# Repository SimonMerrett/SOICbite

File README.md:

# SOICbite
A compact PCB footprint which allows SOIC test clips to be used as a space-efficient programming and debugging connector

This is the repository for a hackaday.io project on this connector footprint.

It's cheaper than a Tag Connect and may even be smaller. 

This has been tested as a SPI programmer on AVRs and a UART programmer on ESP32.

The footprints are available in the following formats:

- Kicad (.kicad_mod)
- Eagle XML (.lbr)
- gEDA PCB (.fp)
- pcb-rnd (.lht)

and more formats are welcome.

You do need to [adjust your SOIC-8 test clip](https://github.com/SimonMerrett/SOICbite/blob/master/HOWTO_mod_clip.md) so that it will close enough to press the contact pins against the PCB pads. See the photos in the images folder - about 1mm will do to start with. Depending on your pin configuration, you need to make sure opposing contacts don't touch each other when no PCB is between them. 

Also, you may need to use short sections of thin traces to escape the pads between the NPTH.

# Pin assignment

If you don't know where to start, here are a few suggestions for pin assignments of some interfaces:

| Pin | UART | SPI       | SWIM | SWD   | ESP8266     | USB | I2C | PIC ICSP | JTAG | SWD + UART | UPDI |
| --- | ---- | --------- | ---- | ----- | ----------- | --- | --- | -------- | ---- | ---------- | ---- |
| 1   | Vcc  | Vcc       | Vcc  | Vcc   | Vcc         | Vcc | Vcc | Vcc      | Vcc  | Vcc        | Vcc  |
| 2   | RX2  | CS        |      |       | GPIO0       | D-  |     | Vpp      | TMS  | RX         |      |
| 3   | TX2  |           |      |       | GPIO2       | D+  |     |          | TCK  | TX         |      |
| 4   | GND  | GND       | GND  | GND   | GND         | GND | GND | GND      | GND  | GND        | GND  |
| 5   | RX   | MOSI/MOMI | SWIM | SWDIO | RX          |     | SDA | DAT      | TDI  | SWDIO      | UPDI |
| 6   | TX   | MISO      |      | SWO   | TX          |     |     | AUX      | TDO  | SWO        |      |
| 7   | CTS  | SCK/CLK   |      | SWCLK | CH_PD       |     | SCL | CLK      | RTCK | SWCLK      |      |
| 8   | RTS  | RST       | NRST | NRST  | RST         | ID  |     |          | NRST | NRST       |      |

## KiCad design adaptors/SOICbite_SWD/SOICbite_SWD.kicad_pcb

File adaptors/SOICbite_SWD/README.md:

# SOICbite SWD Breakout

SOICbite to SWD breakout board:

1. Standard Cortex Debug connector - VCC, GND, SWDIO, SWCLK, SWO and NRST pins are broken out
2. 4-Pin 2.54" Header - VCC, SWDIO, SWCLK, GND are broken out

## 3D Renders

## Images

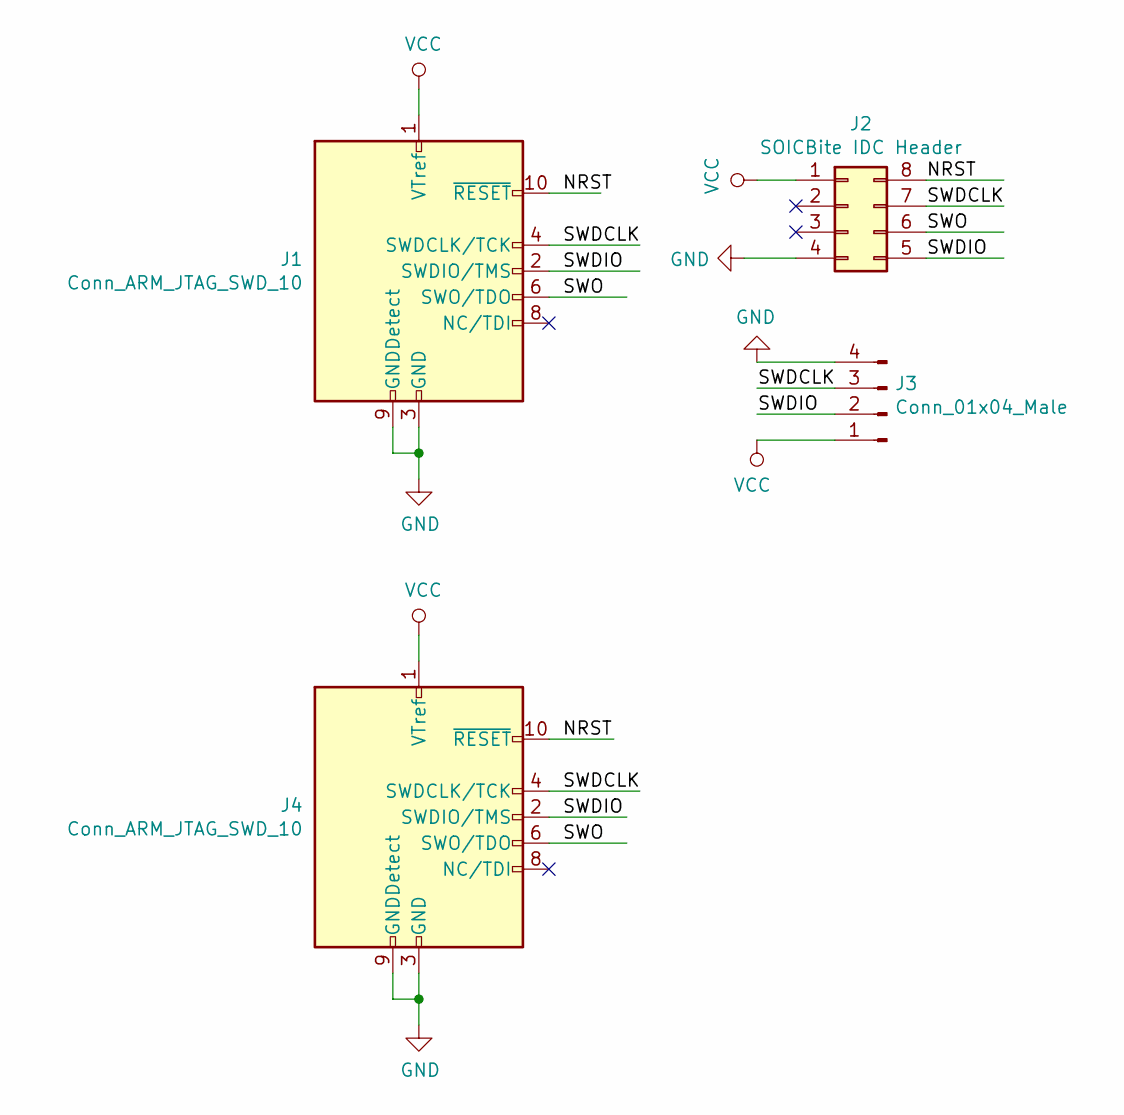
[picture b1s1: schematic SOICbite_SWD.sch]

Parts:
J1: Conn_ARM_JTAG_SWD_10; PinHeader_2x05_P1.27mm_Vertical_SMD
J2: SOICBite IDC Header; IDC-Header_2x04_P2.54mm_Vertical
J3: Conn_01x04_Male; PinHeader_1x04_P2.54mm_Vertical
J4: Conn_ARM_JTAG_SWD_10; PinHeader_2x05_P1.27mm_Vertical

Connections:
/NRST: J1.10 (~RESET~), J2.8, J4.10 (~RESET~)
/SWDCLK: J1.4 (SWDCLK/TCK), J2.7, J3.3, J4.4 (SWDCLK/TCK)
/SWDIO: J1.2 (SWDIO/TMS), J2.5, J3.2, J4.2 (SWDIO/TMS)
/SWO: J1.6 (SWO/TDO), J2.6, J4.6 (SWO/TDO)
GND: J1.3 (GND), J1.5 (GND), J1.9 (GNDDetect), J2.4, J3.4, J4.3 (GND), J4.5 (GND), J4.9 (GNDDetect)
VCC: J1.1 (VTref), J2.1, J3.1, J4.1 (VTref)

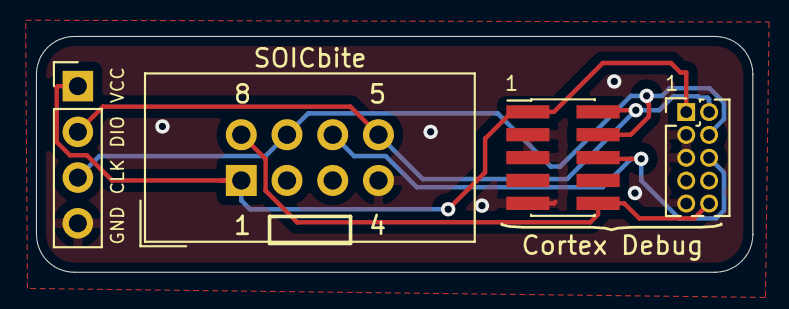
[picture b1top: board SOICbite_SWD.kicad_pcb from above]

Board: 2 copper layers, 39.8 x 13.1 mm, 4 parts (0 on the bottom side), 6 nets.

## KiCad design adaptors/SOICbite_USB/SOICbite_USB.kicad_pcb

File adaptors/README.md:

# Adaptors

Opinionated boards to breakout the SOICbite connections to standard interface pin arrangements.

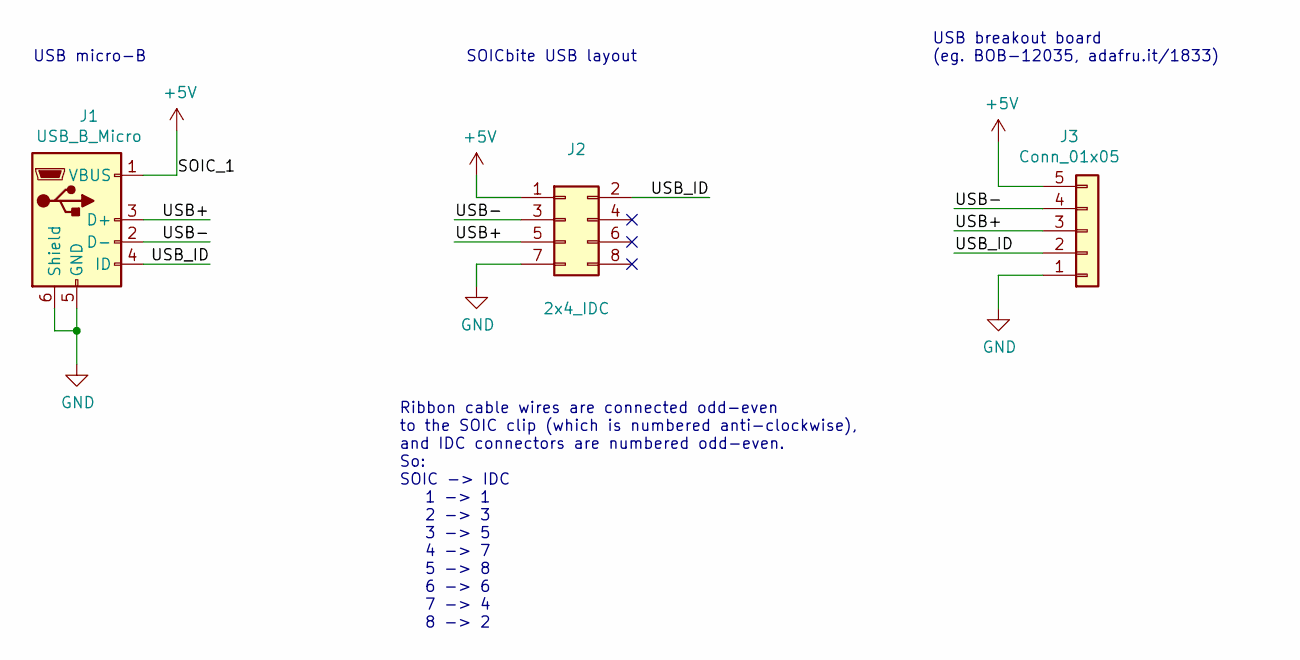
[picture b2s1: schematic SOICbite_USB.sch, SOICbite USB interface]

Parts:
J1: USB_B_Micro; USB_Micro-B_Wuerth_614105150721_Vertical; MPN 614 105 150 721; farnell 2470821
J2: 2x4_IDC; IDC-Header_2x04_P2.54mm_Vertical; MPN 61200821621; farnell 2356252
J3: Conn_01x05; PinHeader_1x05_P2.54mm_Vertical

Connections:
+5V: J1.1 (VBUS), J2.1, J3.5
/USB+: J1.3 (D+), J2.5, J3.3
/USB-: J1.2 (D-), J2.3, J3.4
/USB_ID: J1.4 (ID), J2.2, J3.2
GND: J1.5 (GND), J1.6 (Shield), J2.7, J3.1

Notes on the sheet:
USB micro-B
SOICbite USB layout
USB breakout board (eg. BOB-12035, adafru.it/1833)
Ribbon cable wires are connected odd-even to the SOIC clip (which is numbered anti-clockwise), and IDC connectors are numbered odd-even. So: SOIC -> IDC 1 -> 1 2 -> 3 3 -> 5 4 -> 7 5 -> 8 6 -> 6 7 -> 4 8 -> 2

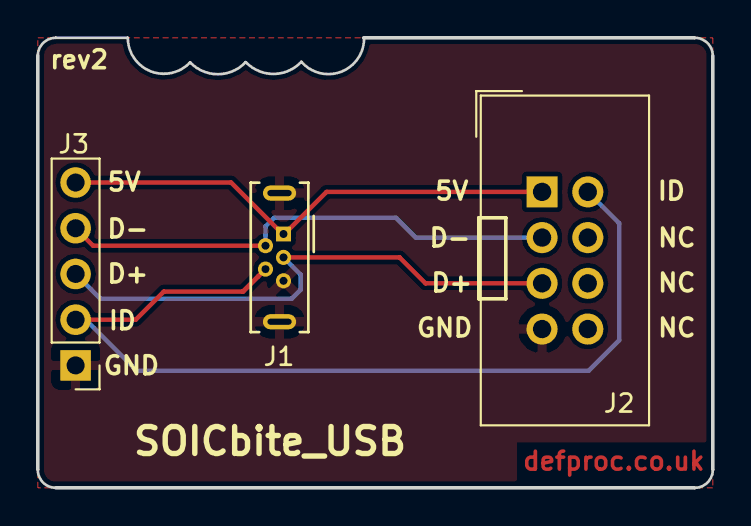
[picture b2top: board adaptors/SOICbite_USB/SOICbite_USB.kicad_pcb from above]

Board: 2 copper layers, 37.5 x 25.0 mm, 3 parts (0 on the bottom side), 5 nets.

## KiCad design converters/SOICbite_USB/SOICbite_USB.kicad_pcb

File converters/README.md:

#Converters

Opinionated boards to breakout the SOICbite connections to standard interface pin arrangements.

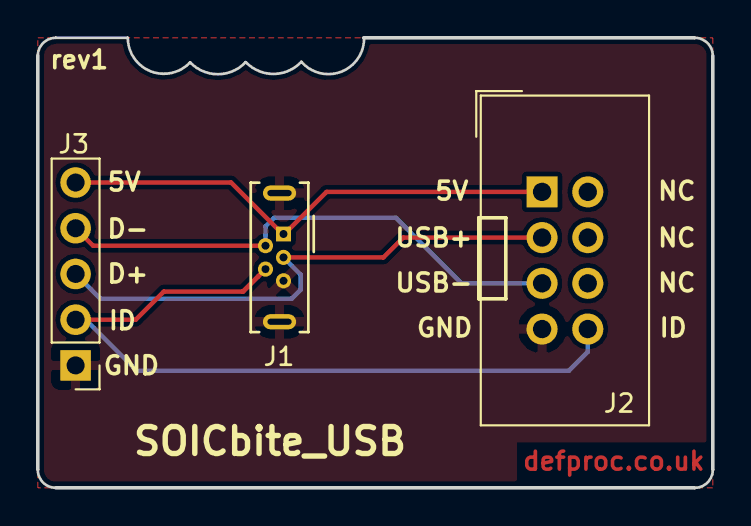
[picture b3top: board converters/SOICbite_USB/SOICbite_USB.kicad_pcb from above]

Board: 2 copper layers, 37.5 x 25.0 mm, 3 parts (0 on the bottom side), 5 nets.

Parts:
J1: USB_B_Micro; USB_Micro-B_Wuerth_614105150721_Vertical
J2: 2x4_IDC; IDC-Header_2x04_P2.54mm_Vertical
J3: Conn_01x05; PinHeader_1x05_P2.54mm_Vertical

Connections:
+5V: J1.1, J2.1, J3.5
/USB+: J1.3, J2.3, J3.3
/USB-: J1.2, J2.5, J3.4
/USB_ID: J1.4, J2.8, J3.2
GND: J1.5, J1.6, J2.7, J3.1

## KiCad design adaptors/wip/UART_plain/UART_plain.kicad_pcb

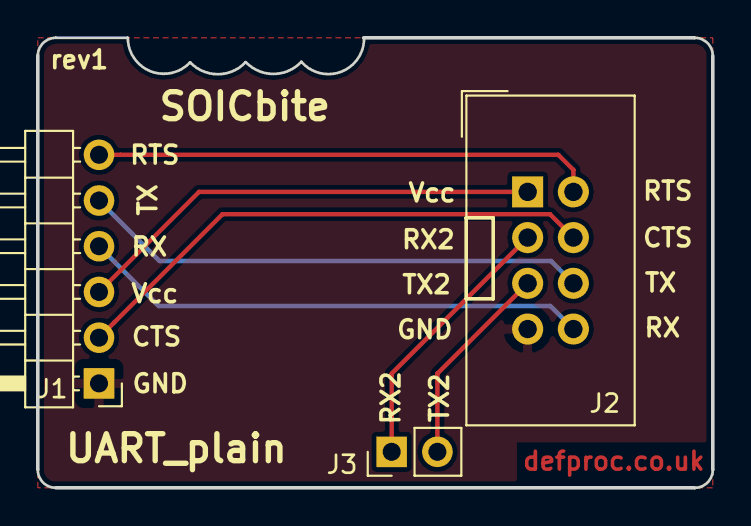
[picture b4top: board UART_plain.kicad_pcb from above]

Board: 2 copper layers, 37.5 x 25.0 mm, 3 parts (0 on the bottom side), 8 nets.

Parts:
J1: UART adaptor; PinHeader_1x06_P2.54mm_Horizontal
J2: 2x4_IDC; IDC-Header_2x04_P2.54mm_Vertical
J3: UART2; PinHeader_1x02_P2.54mm_Vertical

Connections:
/CTS: J1.2, J2.4
/RTS: J1.6, J2.2
/RX: J1.4, J2.8
/RX2: J2.3, J3.1
/TX: J1.5, J2.6
/TX2: J2.5, J3.2
GND: J1.1, J2.7
VDD: J1.3, J2.1

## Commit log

2019-06-03 Upload SOICbite kicad_mod footprint file
2019-06-03 create folder
2019-06-03 upload image files
2019-06-03 Removed ref to Github, as text was copied from HaD.io
2019-06-13 Purpose a pin assignment
    This is just a starting point to suggest a pin assignment for this
    connector. It would be great if every project with a SOICbite connector
    could be used similar, with the same programmer. Anyhow, a "version 1"
    probably should be discussed somehow with all the pros and cons. This
    one uses the SPI pinout of an AVR AT-Tiny and tries to assign similar
    functions from other interfaces to the same pins.
2019-06-14 Swapping pin 1 - pin 8
2019-06-17 Recreated Footprint within Eagle along with a simple Symbol for EAGLE users in .lbr form. Review added images for footprint and library/component description
2019-06-17 Corrected filename
2019-06-17 Corrected Description inconsistency
2019-06-17 Typo correction. Footprint cleanup.
2019-07-23 SOICbite to USB converter board, rev1
2019-07-23 include render of USB interface board
2019-07-23 do markdown properly
2019-08-02 rev1 of a plain IDC to UART adaptor
2019-08-05 SOICbite_USB is works in testing, moved UART_plain to wip directory, kicad gitignore
2019-08-13 removed wip, moved to wip_uart branch
2019-08-13 rev2 layout, moved USB_ID to SOICbite pin 8
2019-08-13 revised pinout, D- should be by Vcc
2019-08-13 added USB pinout
2019-08-13 and update the silkscreen to match the D+/D- swap
2019-08-14 Fixed possible typo in Adapter/adaptor
2019-09-28 Added suggested pinout for I2C
2019-09-29 Add SOICbite to SWD adaptor board
2019-11-11 Update README.md
    added NRST to SWD suggested pinout
2019-11-11 Added images for SWD breakout
2019-12-13 Added recommend PIC ICSP pinout
2019-12-20 Clarified "PIC ICSP" instead of any other kind
2020-03-28 Create LICENSE
2020-04-16 Add clip edge detailed image
    May be useful for someone wanting to see better how to trim down their clip
2020-04-16 Create HOWTO_mod_clip.md
    May be helpful for people to visualise the trimming requirement.
2020-04-16 Add README link to HOWTO
2020-06-02 Upload drawing to indicate board edges
    Careful - these dimensions have yet to be fully confirmed but you should be fine using them to make your own footprint from.
2020-06-20 kicad: add courtyard around symbol
    It is good to have courtyard defined as DRC might use it to catch errors
    when components are missing. While it doesn't sound that useful for this
    particular part, the DRC might actually complain about it being missing
    if its turned on for the project.
    The courtyard layer is defined on:
    https://kicad-pcb.org/libraries/klc/F5.3/
2021-02-11 add gEDA footprint and symbol
2021-02-11 add gerbers and images for gEDA footprint
2021-02-11 remove backup files
2022-04-21 Add footprint for pcb-rnd
2022-04-21 Mention various formats available
2022-04-21 Update readme with avaliable formats
2022-04-21 Update README with available formats
2023-11-25 Add JTAG pin specification
2024-11-02 Add SWD+UART pin assignment
2025-08-10 Add UPDI pinout
    Modify UART pinout to put UPDI on RX pin

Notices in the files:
adaptors/SOICbite_SWD/SOICbite_SWD.kicad_pcb:
© 2019, Uri Shaked
